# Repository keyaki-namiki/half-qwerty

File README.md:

[reference](https://youtu.be/_M2C5gomEkM?t=2003)

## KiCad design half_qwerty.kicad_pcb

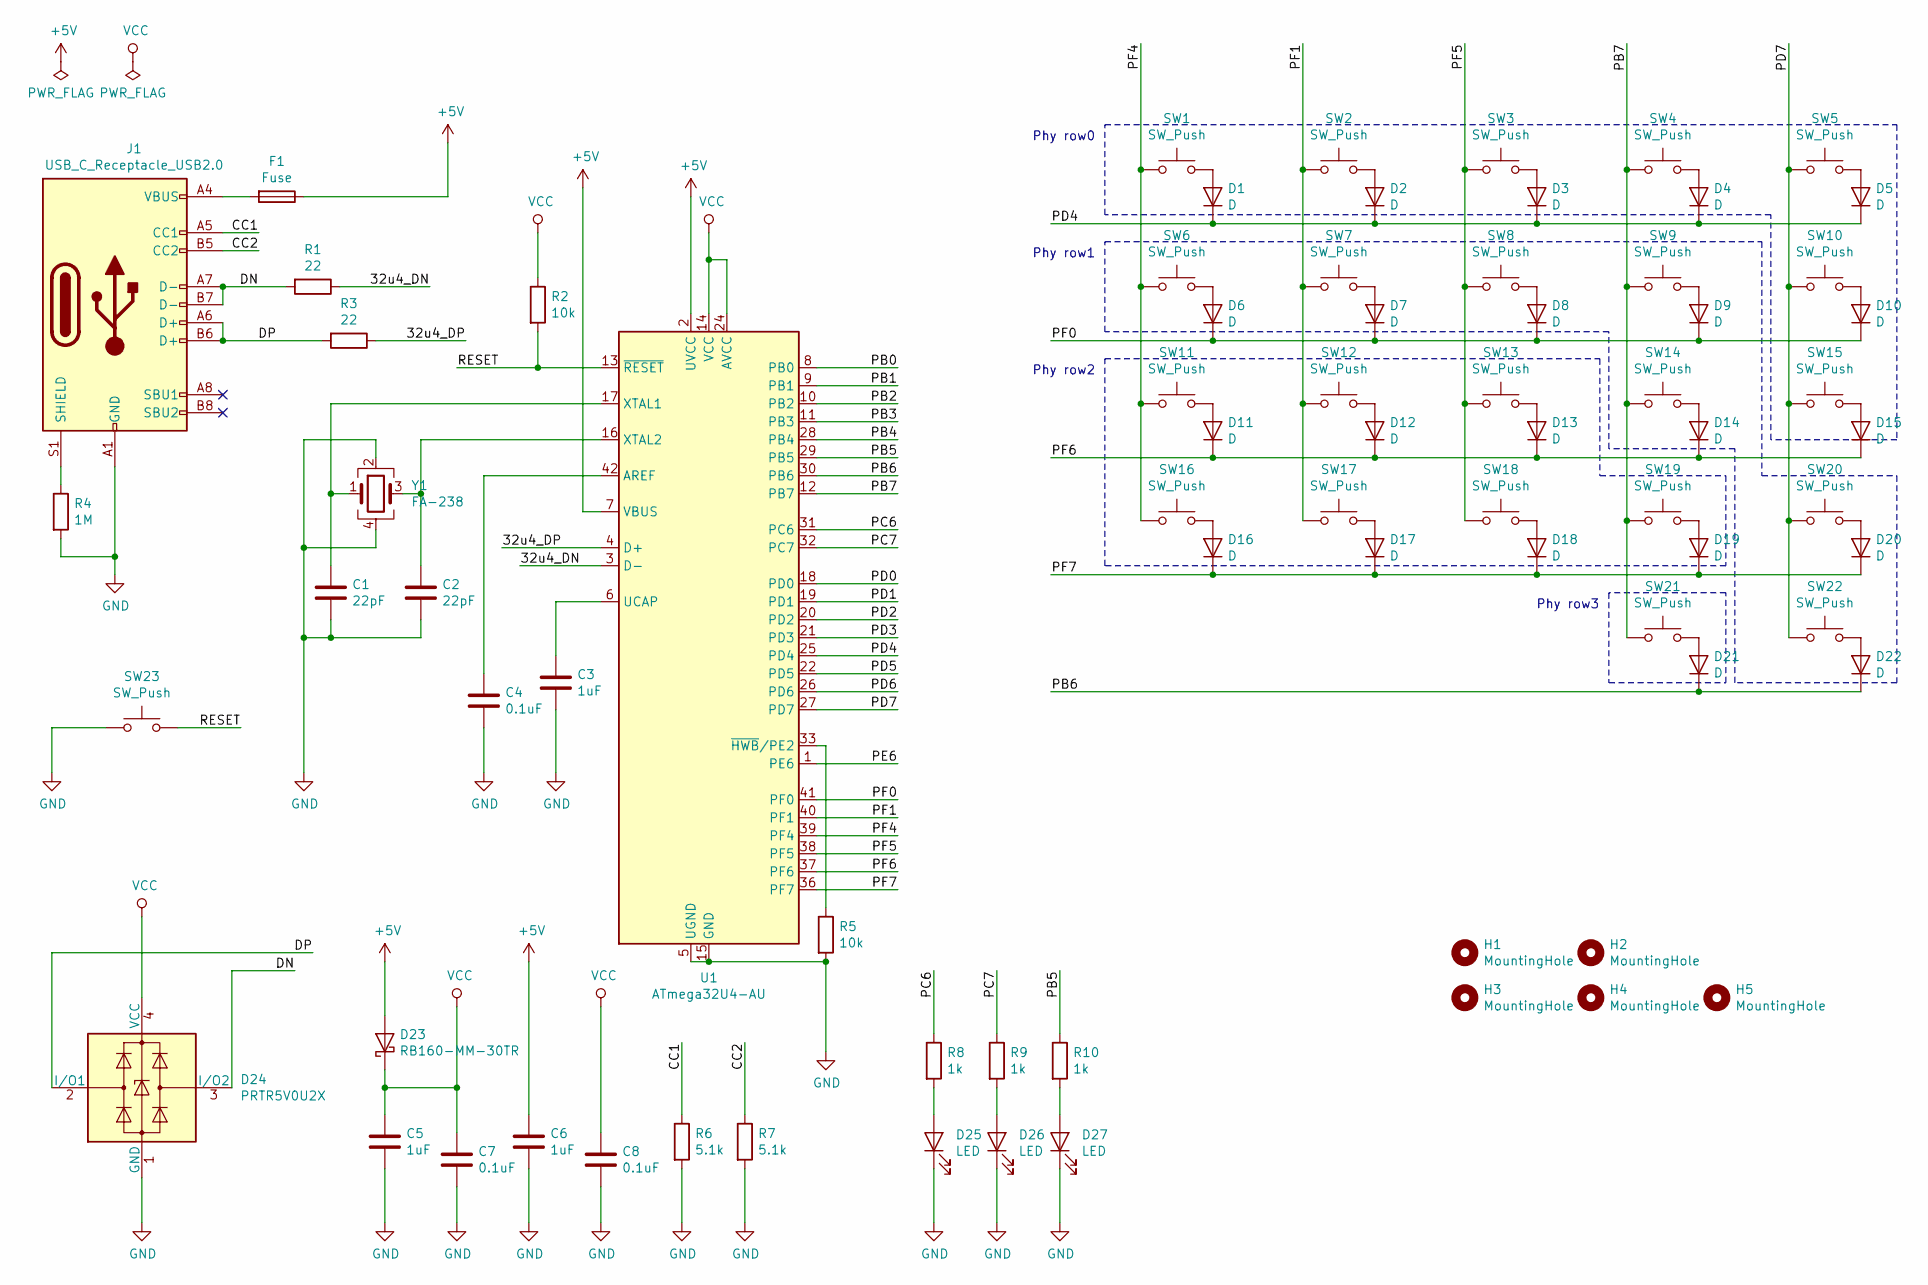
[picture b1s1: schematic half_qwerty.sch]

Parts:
C1, C2: 22pF; C_0603_1608Metric_Pad1.05x0.95mm_HandSolder
C3, C5, C6: 1uF; C_0603_1608Metric_Pad1.05x0.95mm_HandSolder
C4, C7, C8: 0.1uF; C_0603_1608Metric_Pad1.05x0.95mm_HandSolder
D1, D2, D3, D4, D5, D6, D7, D8, D9, D10, D11, D12, D13, D14, D15, D16, D17, D18, D19, D20, D21, D22: D; D_SOD-123
D23: RB160-MM-30TR; D_SOD-123F
D24: PRTR5V0U2X; SOT-143
D25, D26, D27: LED; LED_0805_2012Metric_Pad1.15x1.40mm_HandSolder
F1: Fuse; Fuse_1206_3216Metric_Pad1.42x1.75mm_HandSolder
H1, H2, H3, H4, H5: MountingHole; MountingHole_2.2mm_M2_Pad-noREFs
J1: USB_C_Receptacle_USB2.0; USB_C_Receptacle_GCT_USB4085-reAnchored
R1, R3: 22; R_0603_1608Metric_Pad1.05x0.95mm_HandSolder
R2, R5: 10k; R_0603_1608Metric_Pad1.05x0.95mm_HandSolder
R4: 1M; R_0603_1608Metric_Pad1.05x0.95mm_HandSolder
R6, R7: 5.1k; R_0603_1608Metric_Pad1.05x0.95mm_HandSolder
R8, R9, R10: 1k; R_0603_1608Metric_Pad1.05x0.95mm_HandSolder
SW1, SW2, SW3, SW4, SW5, SW7, SW8, SW9, SW10, SW12, SW13, SW14, SW16, SW17, SW18, SW19, SW20: SW_Push; MXOnly-1U-Hotswap
SW6, SW22: SW_Push; MXOnly-1.25U-Hotswap
SW11, SW15: SW_Push; MXOnly-1.5U-Hotswap
SW21: SW_Push; MXOnly-2.75U-Hotswap-ReversedStabilizers
SW23: SW_Push; SW_SPST_TL3342
U1: ATmega32U4-AU; TQFP-44_10x10mm_P0.8mm
Y1: FA-238; Crystal_SMD_SeikoEpson_FA238-4Pin_3.2x2.5mm

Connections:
+5V: C6.1, D23.2 (A), F1.1, U1.2 (UVCC), U1.7 (VBUS)
/32u4_DN: R1.1, U1.3 (D-)
/32u4_DP: R3.1, U1.4 (D+)
/CC1: J1.A5 (CC1), R6.1
/CC2: J1.B5 (CC2), R7.1
/DN: D24.3 (I/O2), J1.A7 (D-), J1.B7 (D-), R1.2
/DP: D24.2 (I/O1), J1.A6 (D+), J1.B6 (D+), R3.2
/PB0: U1.8 (PB0)
/PB1: U1.9 (PB1)
/PB2: U1.10 (PB2)
/PB3: U1.11 (PB3)
/PB4: U1.28 (PB4)
/PB5: R10.1, U1.29 (PB5)
/PB6: D21.1 (K), D22.1 (K), U1.30 (PB6)
/PB7: SW4.1, SW9.1, SW14.1, SW19.1, SW21.1, U1.12 (PB7)
/PC6: R8.1, U1.31 (PC6)
/PC7: R9.1, U1.32 (PC7)
/PD0: U1.18 (PD0)
/PD1: U1.19 (PD1)
/PD2: U1.20 (PD2)
/PD3: U1.21 (PD3)
/PD4: D1.1 (K), D2.1 (K), D3.1 (K), D4.1 (K), D5.1 (K), U1.25 (PD4)
/PD5: U1.22 (PD5)
/PD6: U1.26 (PD6)
/PD7: SW5.1, SW10.1, SW15.1, SW20.1, SW22.1, U1.27 (PD7)
/PE6: U1.1 (PE6)
/PF0: D6.1 (K), D7.1 (K), D8.1 (K), D9.1 (K), D10.1 (K), U1.41 (PF0)
/PF1: SW2.1, SW7.1, SW12.1, SW17.1, U1.40 (PF1)
/PF4: SW1.1, SW6.1, SW11.1, SW16.1, U1.39 (PF4)
/PF5: SW3.1, SW8.1, SW13.1, SW18.1, U1.38 (PF5)
/PF6: D11.1 (K), D12.1 (K), D13.1 (K), D14.1 (K), D15.1 (K), U1.37 (PF6)
/PF7: D16.1 (K), D17.1 (K), D18.1 (K), D19.1 (K), D20.1 (K), U1.36 (PF7)
/RESET: R2.2, SW23.2, U1.13 (~RESET)
GND: C1.2, C2.2, C3.2, C4.2, C5.2, C6.2, C7.2, C8.2, D24.1 (GND), D25.1 (K), D26.1 (K), D27.1 (K), J1.A1 (GND), J1.A12 (GND), J1.B1 (GND), J1.B12 (GND), R4.2, R5.2, R6.2, R7.2, SW23.1, U1.5 (UGND), U1.15 (GND), U1.23 (GND), U1.35 (GND), U1.43 (GND), Y1.2, Y1.4
unnamed: C1.1, U1.17 (XTAL1), Y1.1
unnamed: C2.1, U1.16 (XTAL2), Y1.3
unnamed: C3.1, U1.6 (UCAP)
unnamed: C4.1, U1.42 (AREF)
unnamed: D1.2 (A), SW1.2
unnamed: D2.2 (A), SW2.2
unnamed: D3.2 (A), SW3.2
unnamed: D4.2 (A), SW4.2
unnamed: D5.2 (A), SW5.2
unnamed: D6.2 (A), SW6.2
unnamed: D7.2 (A), SW7.2
unnamed: D8.2 (A), SW8.2
unnamed: D9.2 (A), SW9.2
unnamed: D10.2 (A), SW10.2
unnamed: D11.2 (A), SW11.2
unnamed: D12.2 (A), SW12.2
unnamed: D13.2 (A), SW13.2
unnamed: D14.2 (A), SW14.2
unnamed: D15.2 (A), SW15.2
unnamed: D16.2 (A), SW16.2
unnamed: D17.2 (A), SW17.2
unnamed: D18.2 (A), SW18.2
unnamed: D19.2 (A), SW19.2
unnamed: D20.2 (A), SW20.2
unnamed: D21.2 (A), SW21.2
unnamed: D22.2 (A), SW22.2
unnamed: D25.2 (A), R8.2
unnamed: D26.2 (A), R9.2
unnamed: D27.2 (A), R10.2
unnamed: F1.2, J1.A4 (VBUS), J1.A9 (VBUS), J1.B4 (VBUS), J1.B9 (VBUS)
unnamed: J1.S1 (SHIELD), R4.1
unnamed: R5.1, U1.33 (~HWB~/PE2)
VCC: C5.1, C7.1, C8.1, D23.1 (K), D24.4 (VCC), R2.1, U1.14 (VCC), U1.24 (AVCC), U1.34 (VCC), U1.44 (AVCC)

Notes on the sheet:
Phy row0
Phy row1
Phy row2
Phy row3

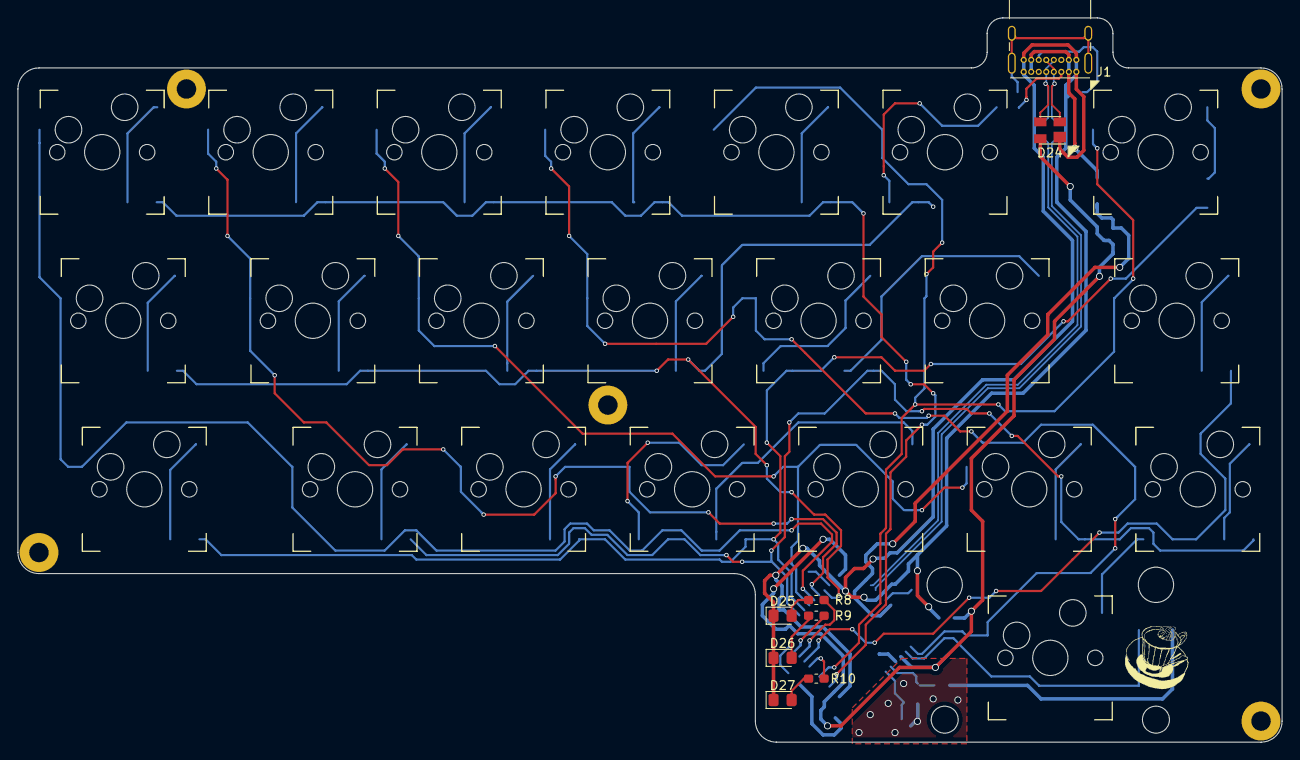
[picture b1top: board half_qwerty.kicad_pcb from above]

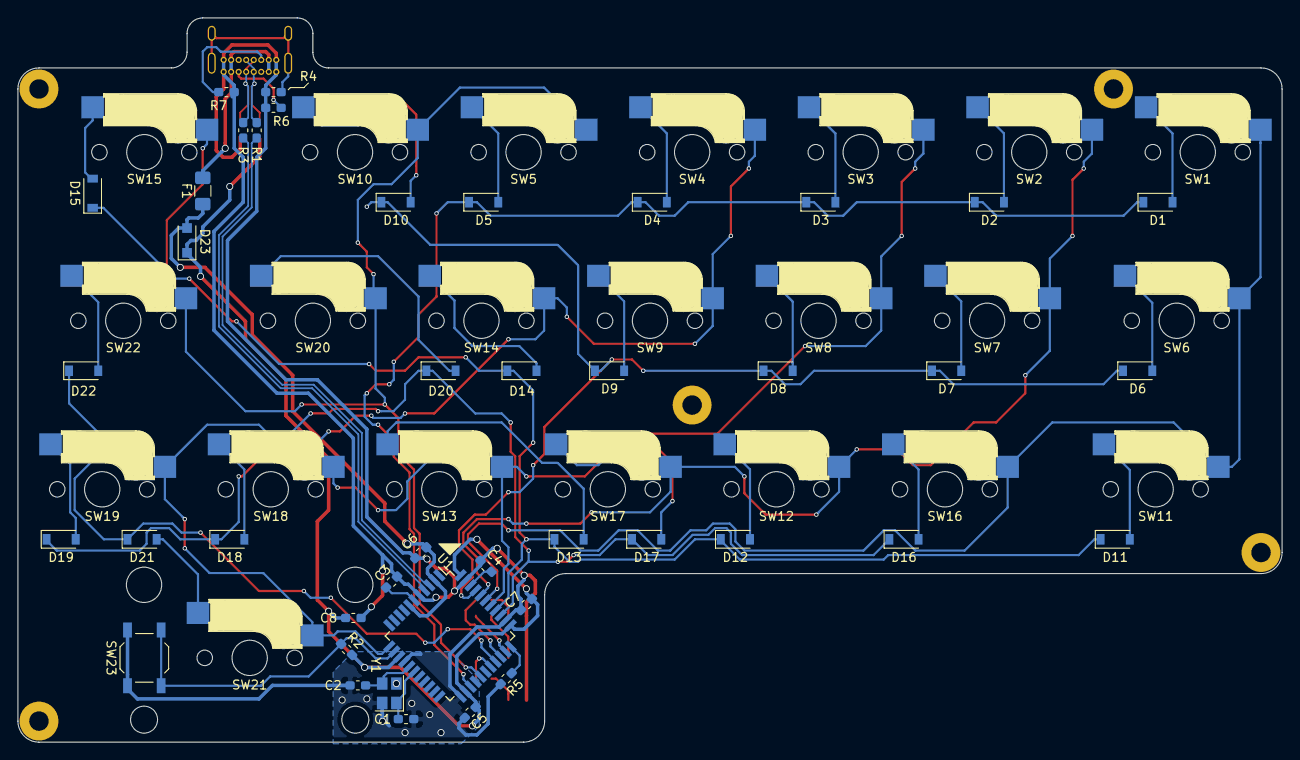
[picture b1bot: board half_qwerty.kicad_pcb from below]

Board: 2 copper layers, 142.9 x 81.9 mm, 77 parts (42 on the bottom side), 55 nets.

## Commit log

2019-12-25 done for now
2019-12-25 generated gerber files
2020-01-04 recheck and var. alpha ordered
